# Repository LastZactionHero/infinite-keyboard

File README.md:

Infinite Keyboard is a portable musical scratchpad. It continously captures of every note played on the integrated keyboard as MIDI data, saved directly to an SD card. This allows you to freely play ideas as they occur, knowing they can always revisit the performance later. The system uses an ESP32-S3 microcontroller, with aPCM5102 DAC and TPA6130A2 headphone amplifier, and supports USB connectivity for potential MIDI output or other functions.

1. ESP32-S3 Module (ESP32-S3-WROOM-1-N8)
    [ ] Power (3.3V):
        [X] Connect module Pin 2 (3V3) to the main 3.3V power rail.
        [X] Connect module Pin 1 and Pin 40 (GND) and EPAD (Pin 41) to the main ground plane.
        [ ] Place bulk decoupling capacitor (10µF - 22µF) near the module between 3.3V and GND.
        [ ] Place local decoupling capacitor (0.1µF - 1µF) very close to Pin 2 (3V3) and GND.
    [X] Enable/Reset Circuit:
        [X] Connect an RC delay circuit to the EN pin (Pin 3): 10kΩ resistor to 3.3V, 1µF capacitor to GND.
        [X] Connect a momentary push button (Reset Switch) between EN (Pin 3) and GND.
    [X] Boot Mode Circuit:
        [X] Connect a 10kΩ pull-up resistor from GPIO0 (Pin 27) to 3.3V.
        [X] Connect a momentary push button (Boot Switch) between GPIO0 (Pin 27) and GND.
    [X] Crystal Oscillator: 40 MHz crystal is integrated within the module. No external crystal needed.
    [X] Antenna: Use onboard PCB antenna (WROOM-1). Ensure proper keep-out zones on your PCB as per layout guidelines. [cite: uploaded:esp32_s3_wroom_1_wroom_1u_datasheet_en-2930317.pdf]
2. USB Interface (Native OTG)
    [-] Connections:
        [X] Connect ESP32-S3 GPIO19 (Module Pin 13) to USB Connector D-.
        [X] Connect ESP32-S3 GPIO20 (Module Pin 14) to USB Connector D+.
        [X] Connect USB Connector VBUS to 5V supply (if host mode power required, consider power switching).
        [X] Connect USB Connector GND to main ground.
        [-] Connect USB Connector Shield to main ground.
    [-] Optional Components:
        [X] Place 0Ω series resistors/jumpers on D+/D- lines if desired.
        [-] Place ESD protection diodes (TVS array) near the connector on D+/D- lines.
    [] Layout: Route D+/D- as a 90Ω differential pair.
3. I2S Interface (ESP32-S3 to PCM5102)
    [X] Connections:
        [X] Connect ESP32-S3 GPIO (Select Pin) -> PCM5102 BCK (Pin 13).
        [X] Connect ESP32-S3 GPIO (Select Pin) -> PCM5102 LRCK (Pin 15).
        [X] Connect ESP32-S3 GPIO (Select Pin) -> PCM5102 DIN (Pin 14).
    [X] PCM5102 SCK: Ensure PCM5102 SCK (Pin 12) is connected to GND (to enable internal PLL). [cite: uploaded:pcm5102.pdf]
4. PCM5102 DAC Module
    [X] Power (3.3V):
        [X] Connect CPVDD (Pin 1), AVDD (Pin 8), DVDD (Pin 20) to 3.3V rail.
        [X] Connect CPGND (Pin 3), AGND (Pin 9), DGND (Pin 19) to ground plane (ensure proper analog/digital ground separation if needed, though often a single solid plane works well with careful layout).
        [X] Place 1µF decoupling capacitors close to pins 1, 8, 20 (to GND).
        [X] Place 1µF decoupling capacitor close to pin 18 (LDOO) (to DGND).
    [X] Charge Pump:
        [X] Connect 1µF ceramic capacitor between CAPP (Pin 2) and CAPM (Pin 4).
        [X] Connect 1µF ceramic capacitor from VNEG (Pin 5) to AGND.
    [X] Configuration Pins:
        [X] Connect FMT (Pin 16) to GND (I2S Format).
        [X] Connect FLT (Pin 11) to GND (Normal Latency Filter).
        [X] Connect DEMP (Pin 10) to GND (De-emphasis OFF).
        [X] Connect XSMT (Pin 17) to a selected ESP32-S3 GPIO pin for soft mute control.
    [X] Output Filter (Per Channel):
        [X] Connect 470Ω resistor in series with OUTL (Pin 6).
        [X] Connect 2.2nF capacitor from the output of the 470Ω resistor to AGND.
        [X] Repeat for OUTR (Pin 7).
5. I2C Interface (ESP32-S3 to TPA6130A2)
    [X] Connections:
        [X] Connect ESP32-S3 GPIO (Select SCL Pin) -> TPA6130A2 SCL (Pin 8 on QFN).
        [X] Connect ESP32-S3 GPIO (Select SDA Pin) -> TPA6130A2 SDA (Pin 7 on QFN).
    [X] Pull-up Resistors:
        [X] Connect 4.7kΩ pull-up resistor from SCL line to 3.3V rail.
        [X] Connect 4.7kΩ pull-up resistor from SDA line to 3.3V rail.
6. TPA6130A2 Headphone Amplifier Module
    [X] Power (5V):
        [X] Connect TPA6130A2 pins (e.g., Pin 12, Pin 20 on QFN) to 5V rail.
        [X] Connect TPA6130A2 GND pins (e.g., Pin 3, 9, 10, 13, 19 on QFN) and Thermal Pad (if QFN) to ground plane.
        [X] Place 1µF decoupling capacitors close to pins (to GND).
    [X] Charge Pump:
        [X] Connect 1µF low-ESR ceramic capacitor between CPP (Pin 18 on QFN) and CPN (Pin 17 on QFN).
        [X] Connect 1µF low-ESR ceramic capacitor from (Pin 15/16 on QFN) to GND.
    [X] Input Coupling (Single-Ended):
        [X] Connect PCM5102 Left Output (after filter) -> 0.47µF capacitor -> TPA6130A2 LEFTINM (Pin 1 on QFN).
        [X] Connect TPA6130A2 LEFTINP (Pin 2 on QFN) -> 0.47µF capacitor -> GND.
        [X] Connect PCM5102 Right Output (after filter) -> 0.47µF capacitor -> TPA6130A2 RIGHTINM (Pin 5 on QFN).
        [X] Connect TPA6130A2 RIGHTINP (Pin 4 on QFN) -> 0.47µF capacitor -> GND.
    [ ] Output:
        [X] Connect TPA6130A2 HPLEFT (Pin 14 on QFN) -> 3.5mm Jack Tip.
        [X] Connect TPA6130A2 HPRIGHT (Pin 11 on QFN) -> 3.5mm Jack Ring.
        [X] Connect 3.5mm Jack Sleeve -> GND.
    [X] Control Pins:
        [X] Connect SD (Shutdown) pin (Pin 6 on QFN) -> 10kΩ pull-up resistor -> 5V rail (Hardware Enabled).
7. SD Card Interface (SPI)
    [ ] Connections:
        [X] Connect ESP32-S3 GPIO (Select MOSI Pin) -> MicroSD Socket CMD (Pin 3).
        [X] Connect ESP32-S3 GPIO (Select MISO Pin) -> MicroSD Socket DAT0 (Pin 7).
        [X] Connect ESP32-S3 GPIO (Select SCK Pin) -> MicroSD Socket CLK (Pin 5).
        [X] Connect ESP32-S3 GPIO (Select CS Pin) -> MicroSD Socket DAT3/CS (Pin 2).
        [X] Connect MicroSD Socket VDD (Pin 4) -> 3.3V rail.
        [X] Connect MicroSD Socket VSS (Pin 6) -> GND.
    [ ] Supporting Components:
        [X] Place 0.1µF - 1µF decoupling capacitor near the socket VDD pin (to GND).
        [X] Connect 10kΩ - 50kΩ pull-up resistors from CS, MOSI, MISO, SCK lines to 3.3V rail.
    [ ] Optional: Connect Card Detect (CD) pin from socket (e.g., Pin Cd on MSD-1-A) to an ESP32-S3 GPIO if detection is desired. [cite: uploaded:msd_1_a-3510386.pdf]
8. User Interface
    [X] Keyboard Matrix (6x4):
        [X] Connect 6 Rows to 6 selected ESP32-S3 GPIOs.
        [X] Connect 4 Columns to 4 selected ESP32-S3 GPIOs.
        [X] Ensure diodes are included in the matrix design if required for ghosting prevention.
    [X] Push Buttons (x2):
        [X] Connect each button between a selected ESP32-S3 GPIO and GND.
        [X] Enable internal pull-up resistors on the ESP32-S3 GPIOs or add external pull-up resistors (e.g., 10kΩ to 3.3V).
    [X] LEDs (x2):
        [X] Connect each LED's anode to 3.3V (or other suitable supply).
        [X] Connect each LED's cathode through a current-limiting resistor (e.g., 220Ω - 1kΩ, value depends on LED specs and desired brightness) to a selected ESP32-S3 GPIO.
9. Power Supplies
    [ ] Input: Assume 5V input (e.g., from USB VBUS or external supply).
    [ ] 3.3V Regulator (LDO):
        [ ] Use MIC5504-3.3YM5-TR (SOT23-5 package).
        [ ] Connect LDO VIN pin to 5V input rail.
        [ ] Connect LDO GND pin to main ground plane.
        [ ] Connect LDO EN (Enable) pin to VIN (for always-on operation) or to an ESP32-S3 GPIO for software control.
        [ ] Connect LDO VOUT pin to the 3.3V power rail (supplying ESP32-S3, PCM5102, SD Card, UI pull-ups, etc.).
        [ ] Place input decoupling capacitor (e.g., 1µF ceramic) close to LDO VIN pin (to GND).
        [ ] Place output decoupling capacitor (e.g., 1µF ceramic) close to LDO VOUT pin (to GND). Check MIC5504 datasheet for specific capacitor requirements.
    [ ] 5V Rail: Ensure 5V rail is available for TPA6130A2 and LDO input.
    [ ] Layout: Employ good power supply layout practices (e.g., separate power planes or wide traces, proper decoupling placement).

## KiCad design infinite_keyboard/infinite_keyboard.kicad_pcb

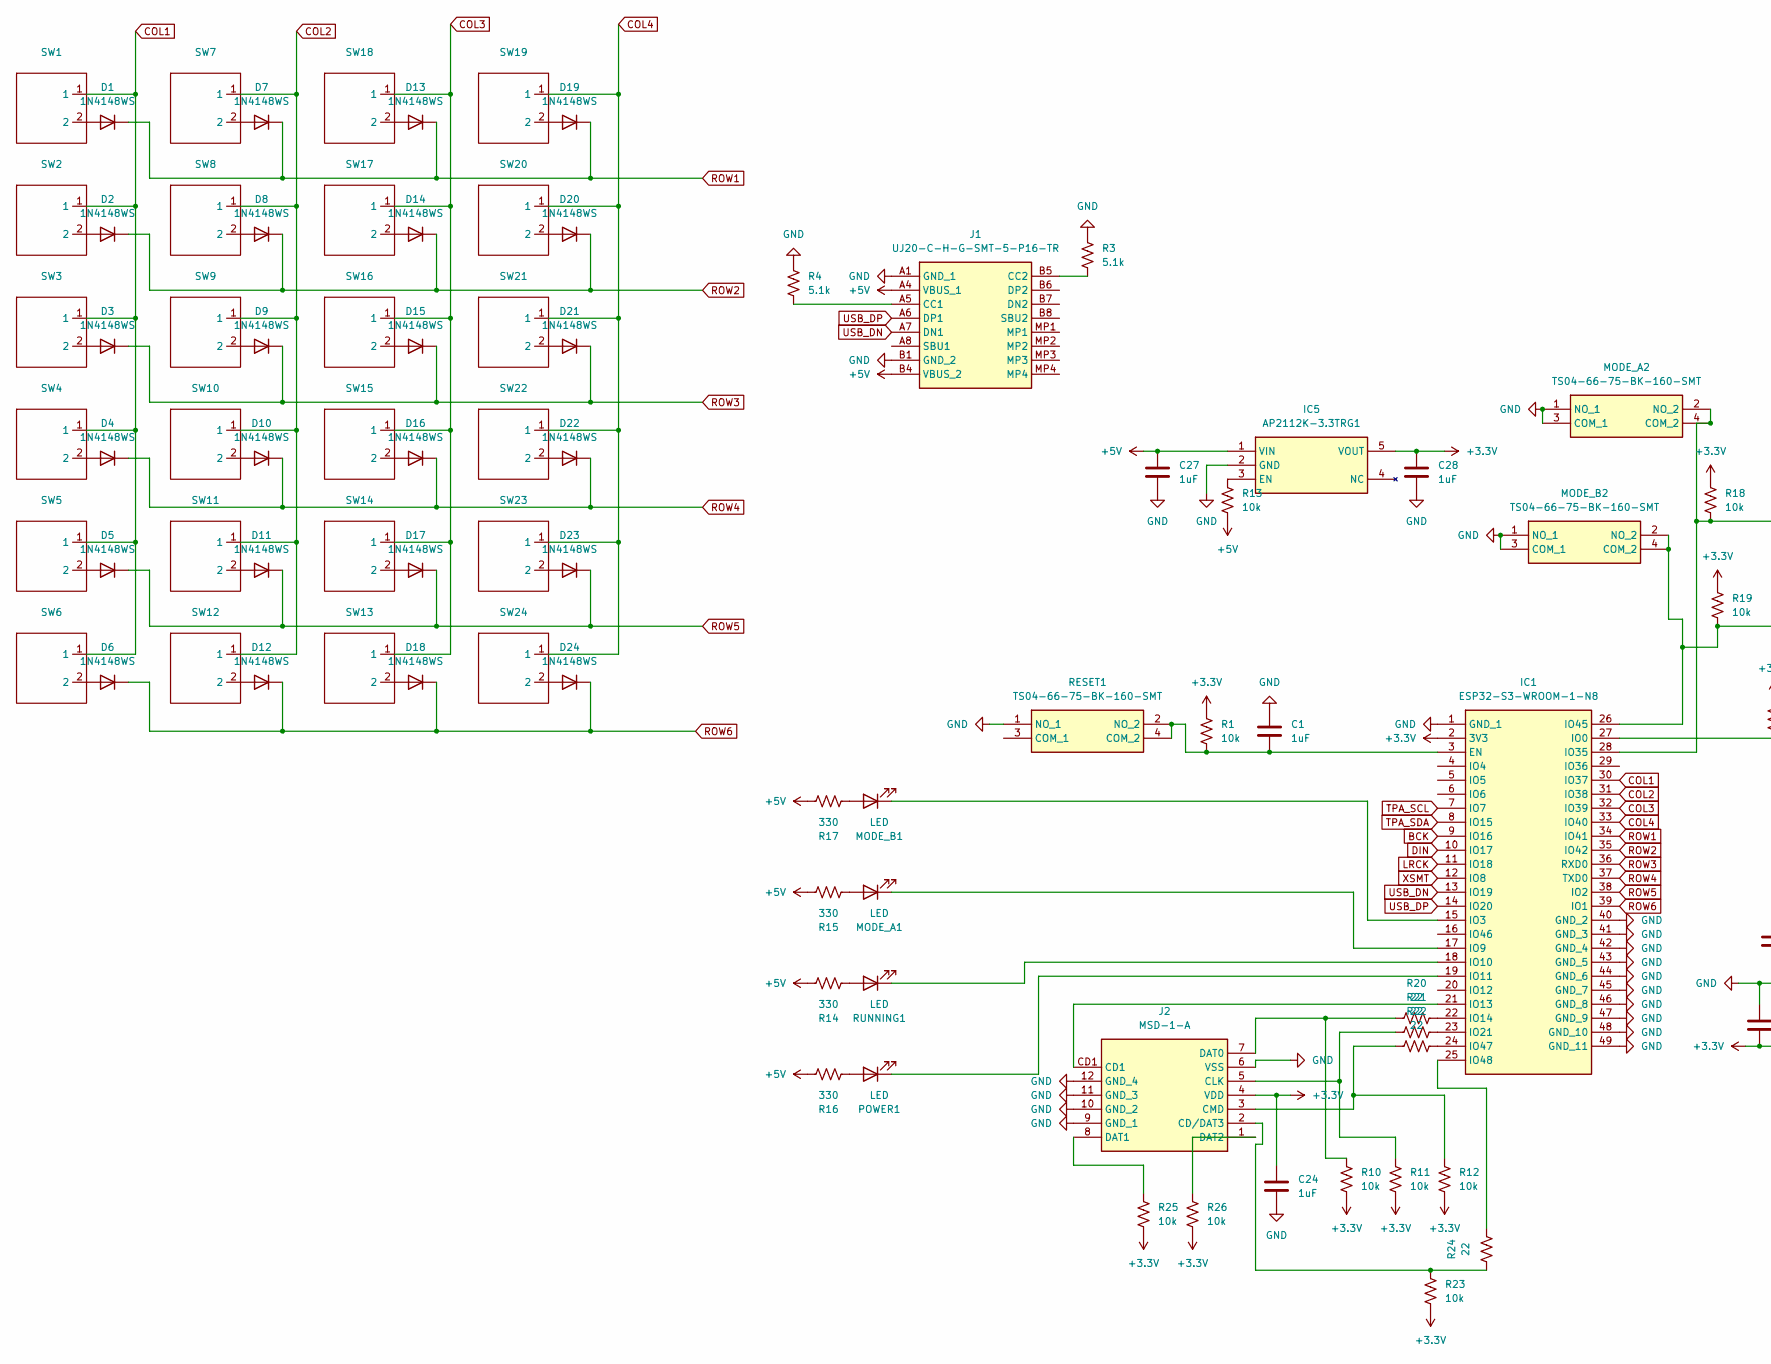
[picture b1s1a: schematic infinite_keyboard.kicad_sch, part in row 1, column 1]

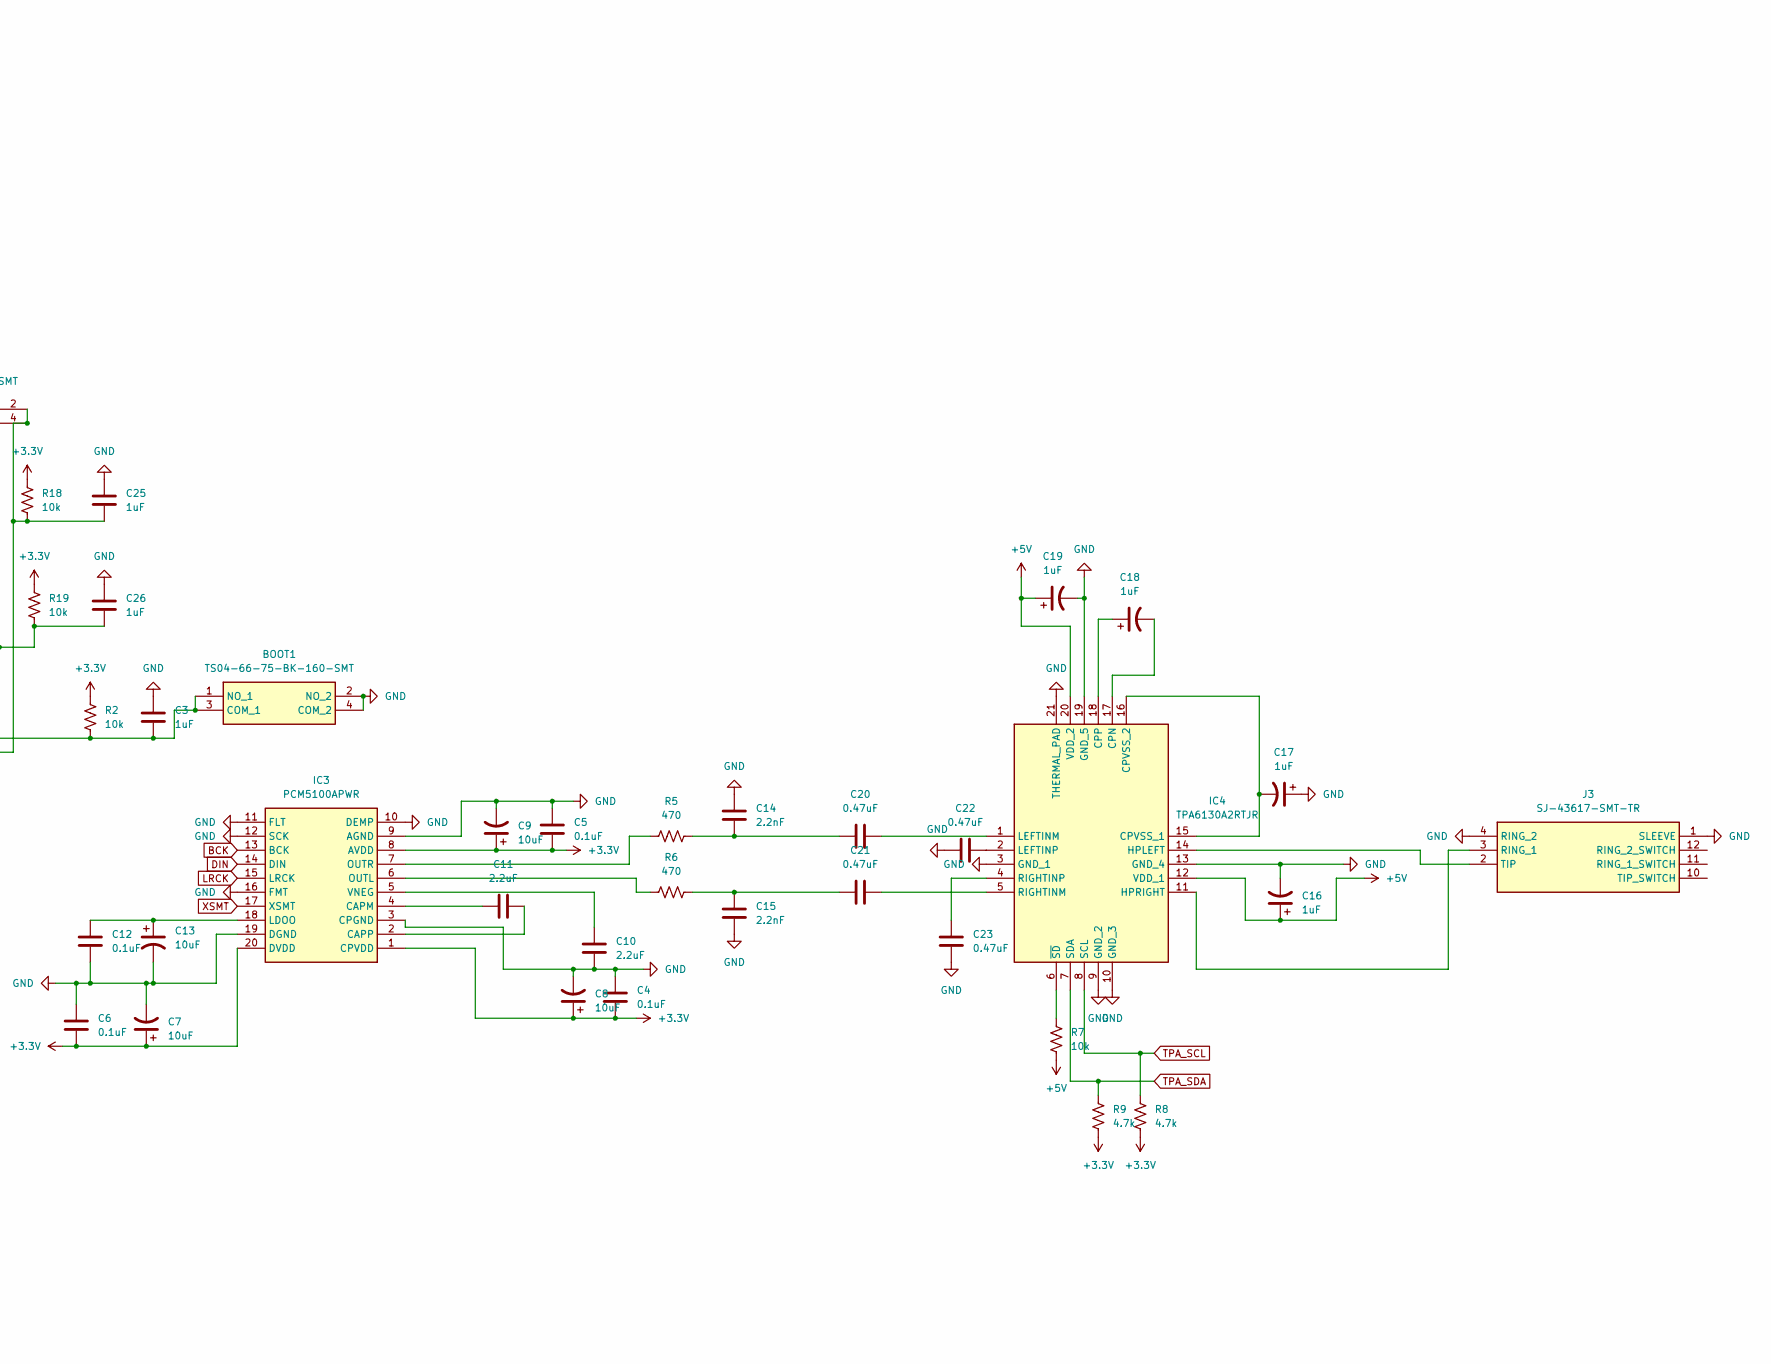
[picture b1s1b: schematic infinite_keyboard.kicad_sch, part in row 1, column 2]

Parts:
BOOT1: TS04-66-75-BK-160-SMT; TS046675BK160SMT; Mouser Part Number 179-TS046675BK160SMT
C1, C3, C16, C17, C18, C19, C24, C25, C26, C27, C28: 1uF; C_0805_2012Metric
C4, C5, C6, C12: 0.1uF; C_0805_2012Metric
C7, C8, C9, C13: 10uF; C_0805_2012Metric
C10, C11: 2.2uF; C_0805_2012Metric
C14, C15: 2.2nF; C_0805_2012Metric
C20, C21, C22, C23: 0.47uF; C_0805_2012Metric
D1, D2, D3, D4, D5, D6, D7, D8, D9, D10, D11, D12, D13, D14, D15, D16, D17, D18, D19, D20, D21, D22, D23, D24: 1N4148WS; D_SOD-323F
IC1: ESP32-S3-WROOM-1-N8; ESP32S3WROOM1N8R2; Mouser Part Number 356-ESP32-S3WROOM1N8
IC3: PCM5100APWR; SOP65P640X120-20N; Mouser Part Number 595-PCM5100APWR
IC4: TPA6130A2RTJR; QFN50P400X400X80-21N-D; Mouser Part Number 595-TPA6130A2RTJR
IC5: AP2112K-3.3TRG1; SOT95P285X140-5N; Mouser Part Number 621-AP2112K-3.3TRG1
J1: UJ20-C-H-G-SMT-5-P16-TR; UJ20CHGSMT5P16TR; Mouser Part Number 179-UJ20CHGSMT5P16TR
J2: MSD-1-A; MSD1A; Mouser Part Number 179-MSD-1-A
J3: SJ-43617-SMT-TR; SJ43617SMTTR; Mouser Part Number 490-SJ-43617-SMT-TR
MODE_A1: LED; LED_0805_2012Metric
MODE_A2: TS04-66-75-BK-160-SMT; TS046675BK160SMT; Mouser Part Number 179-TS046675BK160SMT
MODE_B1: LED; LED_0805_2012Metric
MODE_B2: TS04-66-75-BK-160-SMT; TS046675BK160SMT; Mouser Part Number 179-TS046675BK160SMT
POWER1: LED; LED_0805_2012Metric
R1, R2, R7, R10, R11, R12, R13, R18, R19, R23, R25, R26: 10k; R_0805_2012Metric
R3, R4: 5.1k; R_0805_2012Metric
R5, R6: 470; R_0805_2012Metric
R8, R9: 4.7k; R_0805_2012Metric
R14, R15, R16, R17: 330; R_0805_2012Metric
R20, R21, R22, R24: 22; R_0805_2012Metric
RESET1: TS04-66-75-BK-160-SMT; TS046675BK160SMT; Mouser Part Number 179-TS046675BK160SMT
RUNNING1: LED; LED_0805_2012Metric
SW1, SW2, SW3, SW4, SW5, SW6, SW7, SW8, SW9, SW10, SW11, SW12, SW13, SW14, SW15, SW16, SW17, SW18, SW19, SW20, SW21, SW22, SW23, SW24: CherryMX_1.00u_PCB

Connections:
+3.3V: C4.2, C5.2, C6.2, C7.1, C8.1, C9.1, C24.1, C28.1, IC1.2 (3V3), IC3.1 (CPVDD), IC3.8 (AVDD), IC3.20 (DVDD), IC5.5 (VOUT), J2.4 (VDD), R1.1, R2.1, R8.2, R9.2, R10.2, R11.2, R12.2, R18.1, R19.1, R23.2, R25.2, R26.2
+5V: C16.1, C19.1, C27.1, IC4.12 (VDD_1), IC4.20 (VDD_2), IC5.1 (VIN), J1.A4 (VBUS_1), J1.B4 (VBUS_2), R7.2, R13.2, R14.2, R15.2, R16.2, R17.2
BCK: IC1.9 (IO16), IC3.13 (BCK)
COL1: IC1.30 (IO37), SW1.1, SW2.1, SW3.1, SW4.1, SW5.1, SW6.1
COL2: IC1.31 (IO38), SW7.1, SW8.1, SW9.1, SW10.1, SW11.1, SW12.1
COL3: IC1.32 (IO39), SW13.1, SW14.1, SW15.1, SW16.1, SW17.1, SW18.1
COL4: IC1.33 (IO40), SW19.1, SW20.1, SW21.1, SW22.1, SW23.1, SW24.1
DIN: IC1.10 (IO17), IC3.14 (DIN)
GND: BOOT1.2 (NO_2), BOOT1.4 (COM_2), C1.1, C3.1, C4.1, C5.1, C6.1, C7.2, C8.2, C9.2, C10.2, C12.2, C13.2, C14.1, C15.2, C16.2, C17.1, C19.2, C22.2, C23.2, C24.2, C25.1, C26.1, C27.2, C28.2, IC1.1 (GND_1), IC1.40 (GND_2), IC1.41 (GND_3), IC1.42 (GND_4), IC1.43 (GND_5), IC1.44 (GND_6), IC1.45 (GND_7), IC1.46 (GND_8), IC1.47 (GND_9), IC1.48 (GND_10), IC1.49 (GND_11), IC3.3 (CPGND), IC3.9 (AGND), IC3.10 (DEMP), IC3.11 (FLT), IC3.12 (SCK), IC3.16 (FMT), IC3.19 (DGND), IC4.3 (GND_1), IC4.9 (GND_2), IC4.10 (GND_3), IC4.13 (GND_4), IC4.19 (GND_5), IC4.21 (THERMAL_PAD), IC5.2 (GND), J1.A1 (GND_1), J1.B1 (GND_2), J2.6 (VSS), J2.9 (GND_1), J2.10 (GND_2), J2.11 (GND_3), J2.12 (GND_4), J3.1 (SLEEVE), J3.4 (RING_2), MODE_A2.1 (NO_1), MODE_A2.3 (COM_1), MODE_B2.1 (NO_1), MODE_B2.3 (COM_1), R3.1, R4.1, RESET1.1 (NO_1)
LRCK: IC1.11 (IO18), IC3.15 (LRCK)
unnamed: BOOT1.1 (NO_1), BOOT1.3 (COM_1), C3.2, IC1.27 (IO0), R2.2
unnamed: C14.2, C20.1, R5.2
unnamed: C15.1, C21.1, R6.2
unnamed: D1.2 (A), SW1.2
unnamed: D2.2 (A), SW2.2
unnamed: D3.2 (A), SW3.2
unnamed: D4.2 (A), SW4.2
unnamed: D5.2 (A), SW5.2
unnamed: D6.2 (A), SW6.2
unnamed: D7.2 (A), SW7.2
unnamed: D8.2 (A), SW8.2
unnamed: D9.2 (A), SW9.2
unnamed: D10.2 (A), SW10.2
unnamed: D11.2 (A), SW11.2
unnamed: D12.2 (A), SW12.2
unnamed: D13.2 (A), SW18.2
unnamed: D14.2 (A), SW17.2
unnamed: D15.2 (A), SW16.2
unnamed: D16.2 (A), SW15.2
unnamed: D17.2 (A), SW14.2
unnamed: D18.2 (A), SW13.2
unnamed: D19.2 (A), SW19.2
unnamed: D20.2 (A), SW20.2
unnamed: D21.2 (A), SW21.2
unnamed: D22.2 (A), SW22.2
unnamed: D23.2 (A), SW23.2
unnamed: D24.2 (A), SW24.2
unnamed: C1.2, IC1.3 (EN), R1.2, RESET1.2 (NO_2), RESET1.4 (COM_2)
unnamed: IC1.15 (IO3), MODE_B1.1 (K)
unnamed: IC1.17 (IO9), MODE_A1.1 (K)
unnamed: IC1.18 (IO10), RUNNING1.1 (K)
unnamed: IC1.19 (IO11), POWER1.1 (K)
unnamed: IC1.21 (IO13), J2.CD1
unnamed: IC1.22 (IO14), R20.2
unnamed: IC1.23 (IO21), R21.2
unnamed: C25.2, IC1.28 (IO35), MODE_A2.2 (NO_2), MODE_A2.4 (COM_2), R18.2
unnamed: C26.2, IC1.26 (IO45), MODE_B2.2 (NO_2), MODE_B2.4 (COM_2), R19.2
unnamed: IC1.24 (IO47), R22.2
unnamed: IC1.25 (IO48), R24.2
unnamed: C11.1, IC3.4 (CAPM)
unnamed: C11.2, IC3.2 (CAPP)
unnamed: C12.1, C13.1, IC3.18 (LDOO)
unnamed: IC3.6 (OUTL), R6.1
unnamed: IC3.7 (OUTR), R5.1
unnamed: C10.1, IC3.5 (VNEG)
unnamed: C18.2, IC4.17 (CPN)
unnamed: C18.1, IC4.18 (CPP)
unnamed: C17.2, IC4.15 (CPVSS_1), IC4.16 (CPVSS_2)
unnamed: IC4.14 (HPLEFT), J3.2 (TIP)
unnamed: IC4.11 (HPRIGHT), J3.3 (RING_1)
unnamed: C20.2, IC4.1 (LEFTINM)
unnamed: C22.1, IC4.2 (LEFTINP)
unnamed: C21.2, IC4.5 (RIGHTINM)
unnamed: C23.1, IC4.4 (RIGHTINP)
unnamed: IC4.6 (~SD), R7.1
unnamed: IC5.3 (EN), R13.1
unnamed: J1.A5 (CC1), R4.2
unnamed: J1.B5 (CC2), R3.2
unnamed: J2.2 (CD/DAT3), R23.1, R24.1
unnamed: J2.5 (CLK), R11.1, R21.1
unnamed: J2.3 (CMD), R12.1, R22.1
unnamed: J2.7 (DAT0), R10.1, R20.1
unnamed: J2.8 (DAT1), R25.1
unnamed: J2.1 (DAT2), R26.1
unnamed: MODE_A1.2 (A), R15.1
unnamed: MODE_B1.2 (A), R17.1
unnamed: POWER1.2 (A), R16.1
unnamed: R14.1, RUNNING1.2 (A)
ROW1: D1.1 (K), D7.1 (K), D13.1 (K), D19.1 (K), IC1.34 (IO41)
ROW2: D2.1 (K), D8.1 (K), D14.1 (K), D20.1 (K), IC1.35 (IO42)
ROW3: D3.1 (K), D9.1 (K), D15.1 (K), D21.1 (K), IC1.36 (RXD0)
ROW4: D4.1 (K), D10.1 (K), D16.1 (K), D22.1 (K), IC1.37 (TXD0)
ROW5: D5.1 (K), D11.1 (K), D17.1 (K), D23.1 (K), IC1.38 (IO2)
ROW6: D6.1 (K), D12.1 (K), D18.1 (K), D24.1 (K), IC1.39 (IO1)
TPA_SCL: IC1.7 (IO7), IC4.8 (SCL), R8.1
TPA_SDA: IC1.8 (IO15), IC4.7 (SDA), R9.1
USB_DN: IC1.13 (IO19), J1.A7 (DN1)
USB_DP: IC1.14 (IO20), J1.A6 (DP1)
XSMT: IC1.12 (IO8), IC3.17 (XSMT)

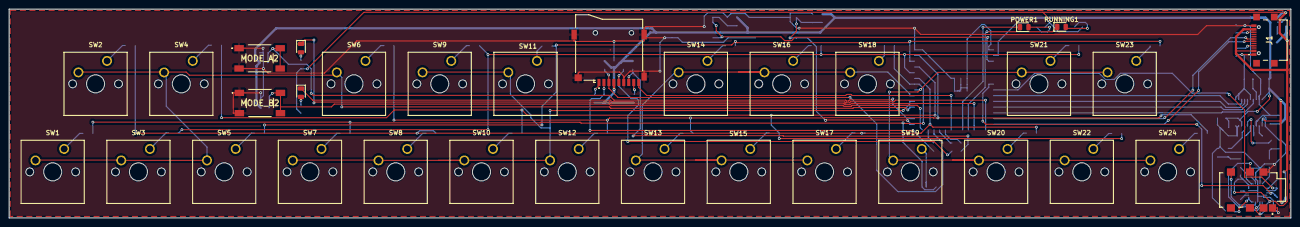
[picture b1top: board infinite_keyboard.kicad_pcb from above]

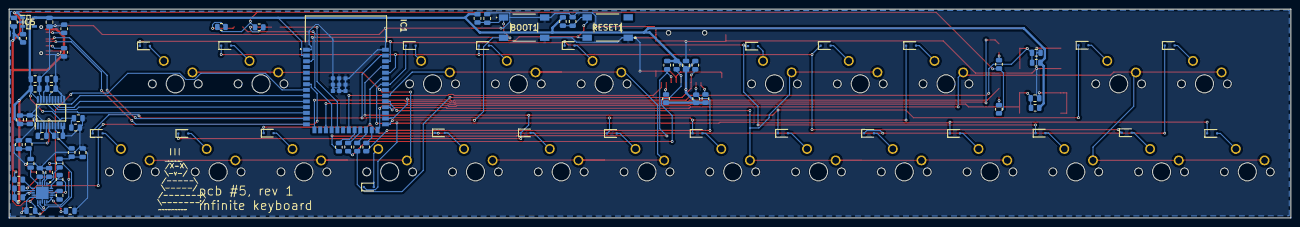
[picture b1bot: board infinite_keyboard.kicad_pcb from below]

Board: 2 copper layers, 283.9 x 46.2 mm, 116 parts (83 on the bottom side), 89 nets.

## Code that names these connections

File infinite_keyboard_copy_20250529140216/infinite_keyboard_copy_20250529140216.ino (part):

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
#define PCM_XSMT_PIN  8  // Soft Mute for DAC (HIGH = un-muted)

#define TPA_SCL_PIN   7  // I2C Clock for TPA6130A2 Amplifier
#define TPA_SDA_PIN   15 // I2C Data for TPA6130A2 Amplifier
#define TPA6130A2_ADDR 0x60 // TPA6130A2 I2C Address (ADDR pin LOW)

#define SAMPLE_RATE         44100
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  // Configure DAC Mute Pin
  pinMode(PCM_XSMT_PIN, OUTPUT);
  digitalWrite(PCM_XSMT_PIN, HIGH); // Un-mute the DAC
  Serial.println("PCM5100A XSMT pin set HIGH (un-muted).");

  // Initialize I2C for TPA6130A2 Amplifier
  Wire.begin(TPA_SDA_PIN, TPA_SCL_PIN);
  Serial.println("I2C interface initialized for TPA6130A2.");
  setup_tpa6130a2();

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
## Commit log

2025-05-09 Initial commit: Project setup with README and .gitignore
2025-05-09 PCB routing
2025-05-12 Lots of updates
2025-05-29 Misc changes
2025-05-29 Add ino file
2025-05-29 Player updates
2025-05-30 keyboard changes
2025-06-02 Synth optimizations
2025-06-02 Rust init
